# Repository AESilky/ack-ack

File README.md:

# ack-ack
Ack-Ack Robot material. This is a combination of data sheets, schematics, drawings, and code.

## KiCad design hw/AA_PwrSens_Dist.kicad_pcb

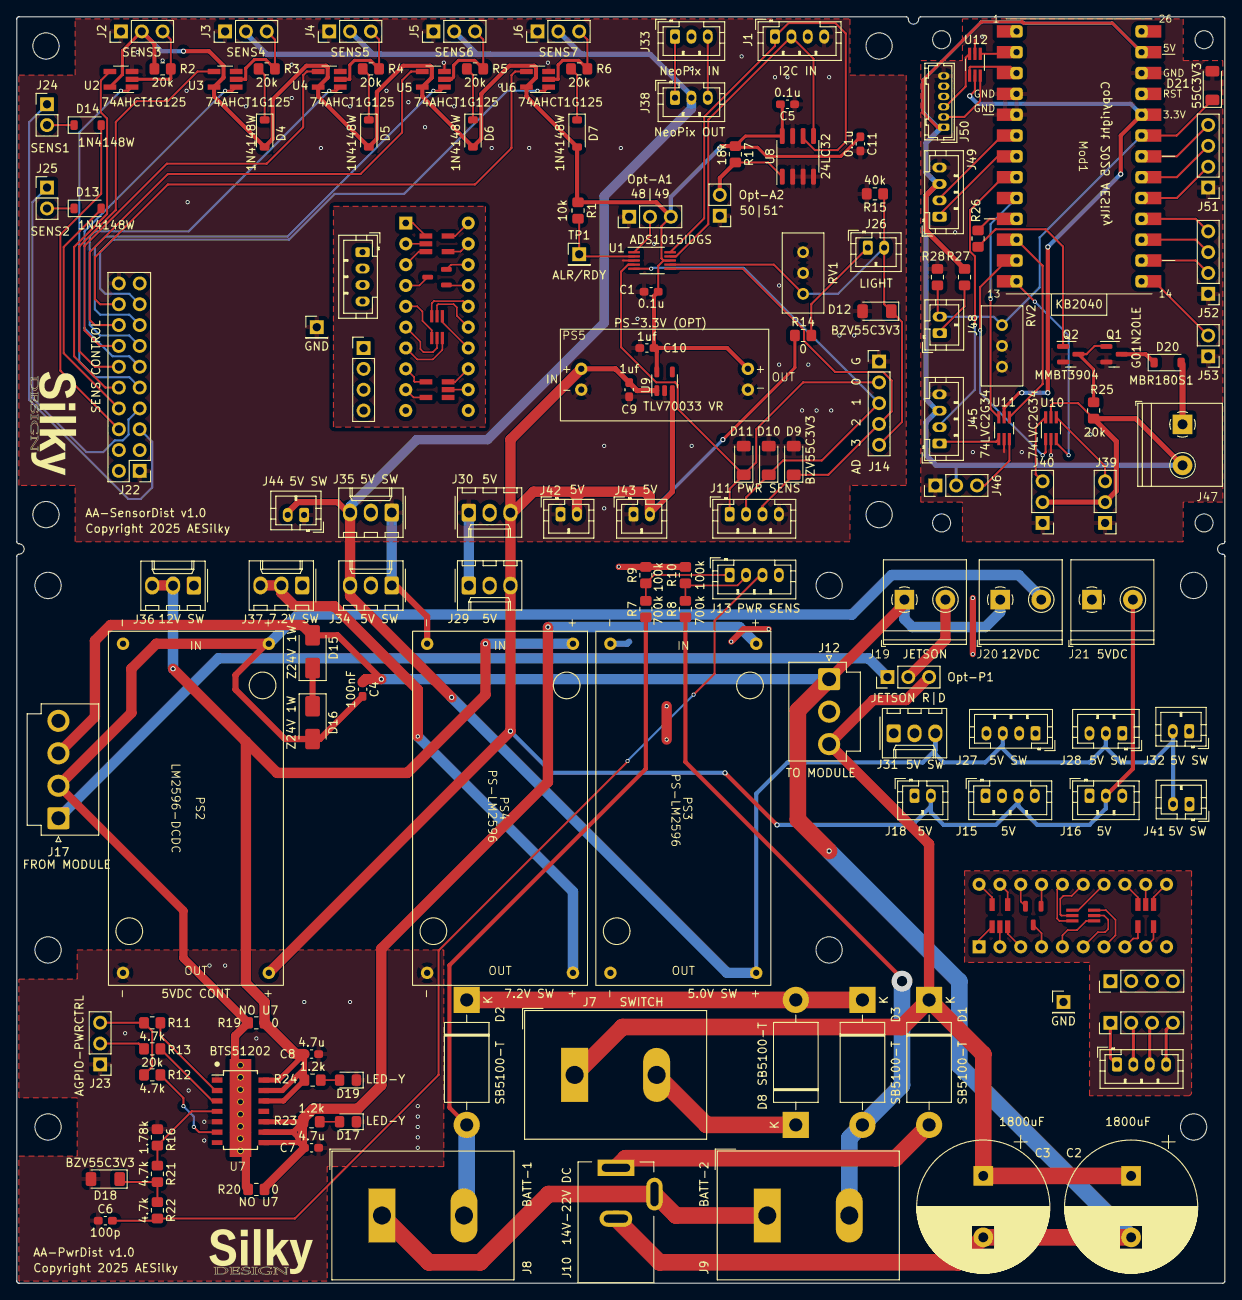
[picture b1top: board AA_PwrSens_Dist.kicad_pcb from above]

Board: 2 copper layers, 147.3 x 154.4 mm, 154 parts (0 on the bottom side), 100 nets.

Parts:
C1, C5, C11: 0.1u; C_0603_1608Metric_Pad1.08x0.95mm_HandSolder
C2, C3: 1800uF; CP_Radial_D16.0mm_P7.50mm
C4: 100nF; C_0603_1608Metric_Pad1.08x0.95mm_HandSolder
C6: 100p; C_0603_1608Metric_Pad1.08x0.95mm_HandSolder
C7, C8: 4.7u; C_0603_1608Metric_Pad1.08x0.95mm_HandSolder
C9, C10: 1uf; C_0603_1608Metric_Pad1.08x0.95mm_HandSolder
D1, D2, D3, D8: SB5100-T; D_DO-201AD_P15.24mm_Horizontal
D4, D5, D6, D7, D13, D14: 1N4148W; D_SOD-123
D9, D10, D11, D12, D18, D21: BZV55C3V3; D_MiniMELF
D15, D16: Z24V 1W; D_SMA
D17, D19: LED-Y; LED_0805_2012Metric_Pad1.15x1.40mm_HandSolder
D20: MBR180S1; D_SOD-123
H1, H2, H3, H4, H5, H6, H7, H8, H9, H10, H11: MountingHole; MountingHole_3.2mm_M3
H13, H14, H15, H16: MH-2mm; MountingHole_2.2mm_M2
J1, J11, J13, J15, J27, J45, J49: JST-PH-B4B; JST_PH_B4B-PH-K_1x04_P2.00mm_Vertical
J2, J3, J4, J5, J6: Conn_01x03; PinHeader_1x03_P2.54mm_Vertical
J7, J8, J9: ScrewLug-2; TerminalBlock_Dinkle_DT-55-B01X-02_P10.00mm
J10: Barrel_Jack_Switch; BarrelJack_Kycon_KLDX-0202-xC_Horizontal
J12: JST-VH-B3P; JST_VH_B3P-VH-B_1x03_P3.96mm_Vertical
J14: Conn_01x05; PinHeader_1x05_P2.54mm_Vertical
J16, J28, J33, J38: JST-PH-B3B; JST_PH_B3B-PH-K_1x03_P2.00mm_Vertical
J17: JST-VH-455-B4P; JST_VH_B4P-VH_1x04_P3.96mm_Vertical
J18, J32, J41: JST-PH-B2B; JST_PH_B2B-PH-K_1x02_P2.00mm_Vertical
J19, J20, J21: SCRW-TERM-2; AES-TermBlock-2POS-5mm-Horz
J22: 20-RBN; PinHeader_2x10_P2.54mm_Vertical
J23: AGPIO-PWRCTRL; PinHeader_1x03_P2.54mm_Vertical
J24, J25: Conn_01x02; PinHeader_1x02_P2.54mm_Vertical
J26, J42, J43, J44, J48: Conn_01x02; JST_PH_B2B-PH-K_1x02_P2.00mm_Vertical
J29, J30, J31, J34, J35, J36, J37: Molex KK-254 AE-6410_1x03; Molex_KK-254_AE-6410-03A_1x03_P2.54mm_Vertical
J39, J40, J46: HDR 1x3 Pin; PinHeader_1x03_P2.54mm_Vertical
J47: ScrewTerm-2; AES-TermBlock-2POS-5mm-Horz
J50: HR-DF13-6P; Hirose_DF13-06P-1.25DSA_1x06_P1.25mm_Vertical
J51, J52: HDR-4; PinHeader_1x04_P2.54mm_Vertical
J53: HDR-2; PinHeader_1x02_P2.54mm_Vertical
Mod1: Adafruit-KB2040-AES
Opt-A1: 3 Pin Hdr; PinHeader_1x03_P2.54mm_Vertical
Opt-A2: Conn_01x02; PinHeader_1x02_P2.54mm_Vertical
Opt-P1: 3 Pin Hdr; PinHeader_1x03_P2.54mm_Vertical
PS2: LM2596-DCDC; DC-DC_Module-AES
PS3, PS4: PS-LM2596; DC-DC_Module-AES
PS5: DC-DC-Mod-1117; DC-DC_Module-SM-44_100-AES
Q1: G01N20LE; SOT-23
Q2: MMBT3904; SOT-23
R1: 10k; R_0805_2012Metric_Pad1.20x1.40mm_HandSolder
R2, R3, R4, R5, R6, R13, R25: 20k; R_0805_2012Metric_Pad1.20x1.40mm_HandSolder
R7, R8: 700.0k; R_0805_2012Metric_Pad1.20x1.40mm_HandSolder
R9, R10: 100.0k; R_0805_2012Metric_Pad1.20x1.40mm_HandSolder
R11, R12, R21, R22: 4.7k; R_0805_2012Metric_Pad1.20x1.40mm_HandSolder
R14, R19, R20, R27: 0; R_0805_2012Metric_Pad1.20x1.40mm_HandSolder
R15, R28: 40k; R_0805_2012Metric_Pad1.20x1.40mm_HandSolder
R16: 1.78k; R_0805_2012Metric_Pad1.20x1.40mm_HandSolder
R17: 18k; R_0805_2012Metric_Pad1.20x1.40mm_HandSolder
R23, R24: 1.2k; R_0805_2012Metric_Pad1.20x1.40mm_HandSolder
R26: 1k; R_0805_2012Metric_Pad1.20x1.40mm_HandSolder
RV1, RV2: 200k; Potentiometer_Bourns_3296W_Vertical
SPR1, SPR1#2: DIP-20_W7.62mm
TP1: 1-Pin; PinHeader_1x01_P2.54mm_Vertical
U1: ADS1015IDGS; VSSOP-10_3x3mm_P0.5mm
U2, U3, U4, U5, U6: 74AHCT1G125; SOT-23-5_HandSoldering
U7: BTS51202; AES-Inf-BTS5120-DSOP14-BP
U8: 24LC32; SOIC-8_3.9x4.9mm_P1.27mm
U9: TLV70033_SOT23-5; SOT-23-5
U10, U11, U12: 74LVC2G34; SOT-363_SC-70-6_Handsoldering

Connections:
+3.3V: C1.2, C5.2, C10.2, C11.1, D4.2 (A), D5.2 (A), D6.2 (A), D7.2 (A), J2.2, Opt-A1.3 (Pin_B), PS5.3 (OUT+), R1.1, R2.1, R17.1, U1.8 (VDD), U2.5 (VCC), U3.5 (VCC), U4.5 (VCC), U5.5 (VCC), U6.5 (VCC), U8.8 (VCC), U9.5 (OUT)
+3.3VP: Mod1.22 (3.3V), U11.5 (VCC), U12.5 (VCC)
+5V: C9.2, J15.3, J16.2, J18.2, J21.2, J29.3, J30.3, J42.2, J43.2, PS2.3 (OUT+), PS5.1 (IN+), R14.1, U9.1 (IN), U9.3 (EN)
+5VD: J3.2, J4.2, J5.2, J6.2, J27.3, J28.2, J31.3, J32.2, J34.3, J35.3, J38.2, J41.2, J44.2, PS3.3 (OUT+)
+5VP: J39.2, J40.2, J45.3, J46.2, J47.2, J49.3, J50.1, Mod1.25 (5V_RAW), R25.2, R27.1, U10.5 (VCC)
+12V: C4.2, D16.2 (A), J17.2, J20.2, PS2.1 (IN+), R19.1, R20.1, U7.CT (VS)
/AA-HeadCtrl/Servo1: J40.3, U10.6
/AA-HeadCtrl/Servo2: J39.3, U10.4
/AIN0: D11.1 (K), J11.1, J14.2, U1.4 (AIN0)
/AIN1: D10.1 (K), J11.2, J14.3, U1.5 (AIN1)
/AIN2: D9.1 (K), J11.3, J14.4, U1.6 (AIN2)
/AIN3: D12.1 (K), J14.5, J26.2, R15.1, RV1.1, U1.7 (AIN3)
/BGND: J8.1, J9.1, J10.3
/BV1: D2.2 (A), J8.2, R7.1
/BV2: D3.2 (A), J9.2, R8.1
/BVC: D2.1 (K), D3.1 (K), D8.2 (A)
/BVC_SW: D8.1 (K), J7.2
/PGND: C2.2, C3.2, C4.1, D15.2 (A), J10.2, J12.1, J17.3, J19.1, J20.1
/PVI: D1.2 (A), J10.1
/PVI_12: J17.1, Opt-P1.1 (Pin_A)
/PVI_SW: C2.1, C3.1, D1.1 (K), J7.1, J12.3, Opt-P1.3 (Pin_B)
/S1-: J22.5, J24.1
/S2-: J22.7, J25.1
/S3-: J22.9, U2.1
/S4-: J22.11, U3.1
/S5-: J22.13, U4.1
/S6-: J22.15, U5.1
/S7-: J22.17, U6.1
/V7_C: J37.2, J37.3, PS4.3 (OUT+)
/V12_C1: C8.2, J36.2, J36.3, PS4.1 (IN+), R19.2, R24.2, U7.12 (OUT0a), U7.13 (OUT0b), U7.14 (OUT0c)
/V12_C2: C7.2, PS3.1 (IN+), R20.2, R23.2, U7.8 (OUT1a), U7.9 (OUT1b), U7.10 (OUT1c)
GND: C1.1, C5.1, C6.1, C7.1, C8.1, C9.1, C10.1, C11.2, D9.2 (A), D10.2 (A), D11.2 (A), D12.2 (A), D17.1 (K), D18.2 (A), D19.1 (K), J1.4, J2.1, J3.1, J4.1, J5.1, J6.1, J11.4, J13.4, J14.1, J15.4, J16.1, J17.4, J18.1, J21.1, J22.1, J22.20, J23.1, J27.4, J28.1, J29.1, J30.1, J31.1, J32.1, J34.1, J35.1, J36.1, J37.1, J41.1, J42.1, J43.1, J44.1, Opt-A1.1 (Pin_A), Opt-A2.1, PS2.2 (IN-), PS2.4 (OUT-), PS3.2 (IN-), PS3.4 (OUT-), PS4.2 (IN-), PS4.4 (OUT-), PS5.2 (IN-), PS5.4 (OUT-), R9.2, R10.2, R15.2, R16.2, RV1.2, RV1.3, U1.3 (GND), U2.3 (GND), U3.3 (GND), U4.3 (GND), U5.3 (GND), U6.3 (GND), U7.1 (GND), U7.5 (DS1), U8.2 (A1), U8.3 (A2), U8.4 (GND), U8.7 (WP), U9.2 (GND)
GND1: D21.2 (A), J39.1, J40.1, J45.4, J46.1, J49.4, J50.6, J51.1, J52.1, J53.1, Mod1.4 (GND), Mod1.5 (GND), Mod1.24 (GND), Q1.2 (S), Q2.2 (E), R28.2, RV2.2, RV2.3, U10.2 (GND), U11.2 (GND), U12.2 (GND)
I2C0_SCL: J1.1, U1.10 (SCL), U8.6 (SCL)
I2C0_SDA: J1.2, U1.9 (SDA), U8.5 (SDA)
unnamed: D4.1 (K), R3.1
unnamed: D5.1 (K), R4.1
unnamed: D6.1 (K), R5.1
unnamed: D7.1 (K), R6.1
unnamed: D13.2 (A), J22.8
unnamed: D13.1 (K), J25.2
unnamed: D14.2 (A), J22.6
unnamed: D14.1 (K), J24.2
unnamed: D15.1 (K), D16.1 (K)
unnamed: D17.2 (A), R23.1
unnamed: D18.1 (K), R21.2, R22.1
unnamed: D19.2 (A), R24.1
unnamed: D20.2 (A), J47.1
unnamed: D20.1 (K), Q1.3 (D)
unnamed: D21.1 (K), J48.2, Mod1.21 (GPIO29_A3), R28.1, RV2.1
unnamed: J2.3, R2.2, U2.2
unnamed: J3.3, R3.2, U3.2
unnamed: J4.3, R4.2, U4.2
unnamed: J5.3, R5.2, U5.2
unnamed: J6.3, R6.2, U6.2
unnamed: J13.1, R7.2, R9.1
unnamed: J13.2, R8.2, R10.1
unnamed: C6.2, J13.3, R22.2
unnamed: J19.2, Opt-P1.2 (Pin_Common)
unnamed: J22.10, U2.4
unnamed: J22.12, U3.4
unnamed: J22.14, U4.4
unnamed: J22.16, U5.4
unnamed: J22.18, U6.4
unnamed: J23.2, R13.1
unnamed: J23.3, R11.1, R12.1
unnamed: J26.1, R14.2
unnamed: J33.1, J38.1
unnamed: J33.3, J38.3
unnamed: J45.1, U11.1
unnamed: J45.2, Mod1.8 (GPIO4_UTX1)
unnamed: J46.3, U11.3
unnamed: J48.1, R27.2
unnamed: J49.1, Mod1.7 (GPIO3_SCL1)
unnamed: J49.2, Mod1.6 (GPIO2_SDA1)
unnamed: J50.2, U12.6
unnamed: J50.3, U12.3
unnamed: J51.2, Mod1.18 (GPIO26_A0)
unnamed: J51.3, Mod1.19 (GPIO27_A1)
unnamed: J51.4, Mod1.20 (GPIO28_A2)
unnamed: J52.2, Mod1.15 (GPIO19_MOSI0)
unnamed: J52.3, Mod1.16 (GPIO20_MISO0)
unnamed: J52.4, Mod1.17 (GPIO18_SCK0)
unnamed: J53.2, Mod1.14 (GPIO10_PWM5A)
unnamed: Mod1.2 (GPIO0_UTX0), U12.1
unnamed: Mod1.3 (GPIO1_URX0), U12.4
unnamed: Mod1.9 (GPIO5_URX1), U11.6
unnamed: Mod1.10 (GPIO6_PWM3A), R26.1
unnamed: Mod1.11 (GPIO7_PWM3B), U11.4
unnamed: Mod1.12 (GPIO8_PWM4A), U10.1
unnamed: Mod1.13 (GPIO9_PWM4B), U10.3
unnamed: Opt-A1.2 (Pin_Common), U1.1 (ADDR)
unnamed: Opt-A2.2, R17.2, U8.1 (A0)
unnamed: Q1.1 (G), Q2.3 (C), R25.1
unnamed: Q2.1 (B), R26.2
unnamed: R1.2, TP1.1, U1.2 (ALERT/RDY)
unnamed: R13.2, U7.3 (DEN)
unnamed: R11.2, U7.2 (IN0)
unnamed: R12.2, U7.6 (IN1)
unnamed: R16.1, R21.1, U7.4 (IS)

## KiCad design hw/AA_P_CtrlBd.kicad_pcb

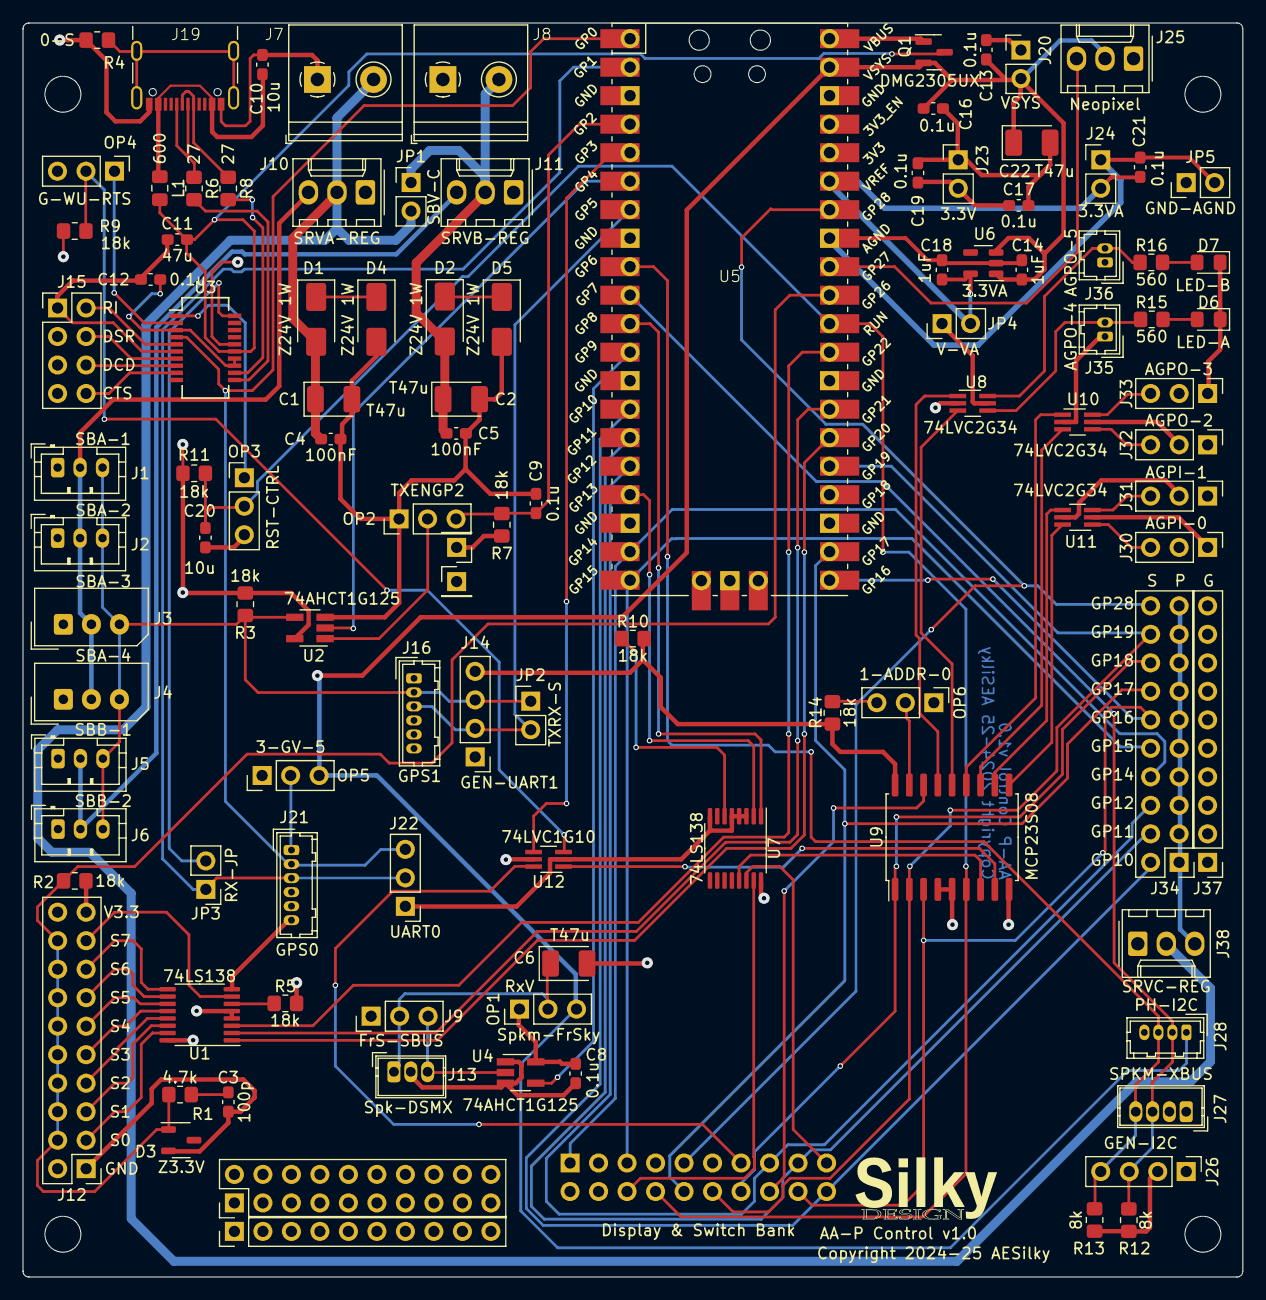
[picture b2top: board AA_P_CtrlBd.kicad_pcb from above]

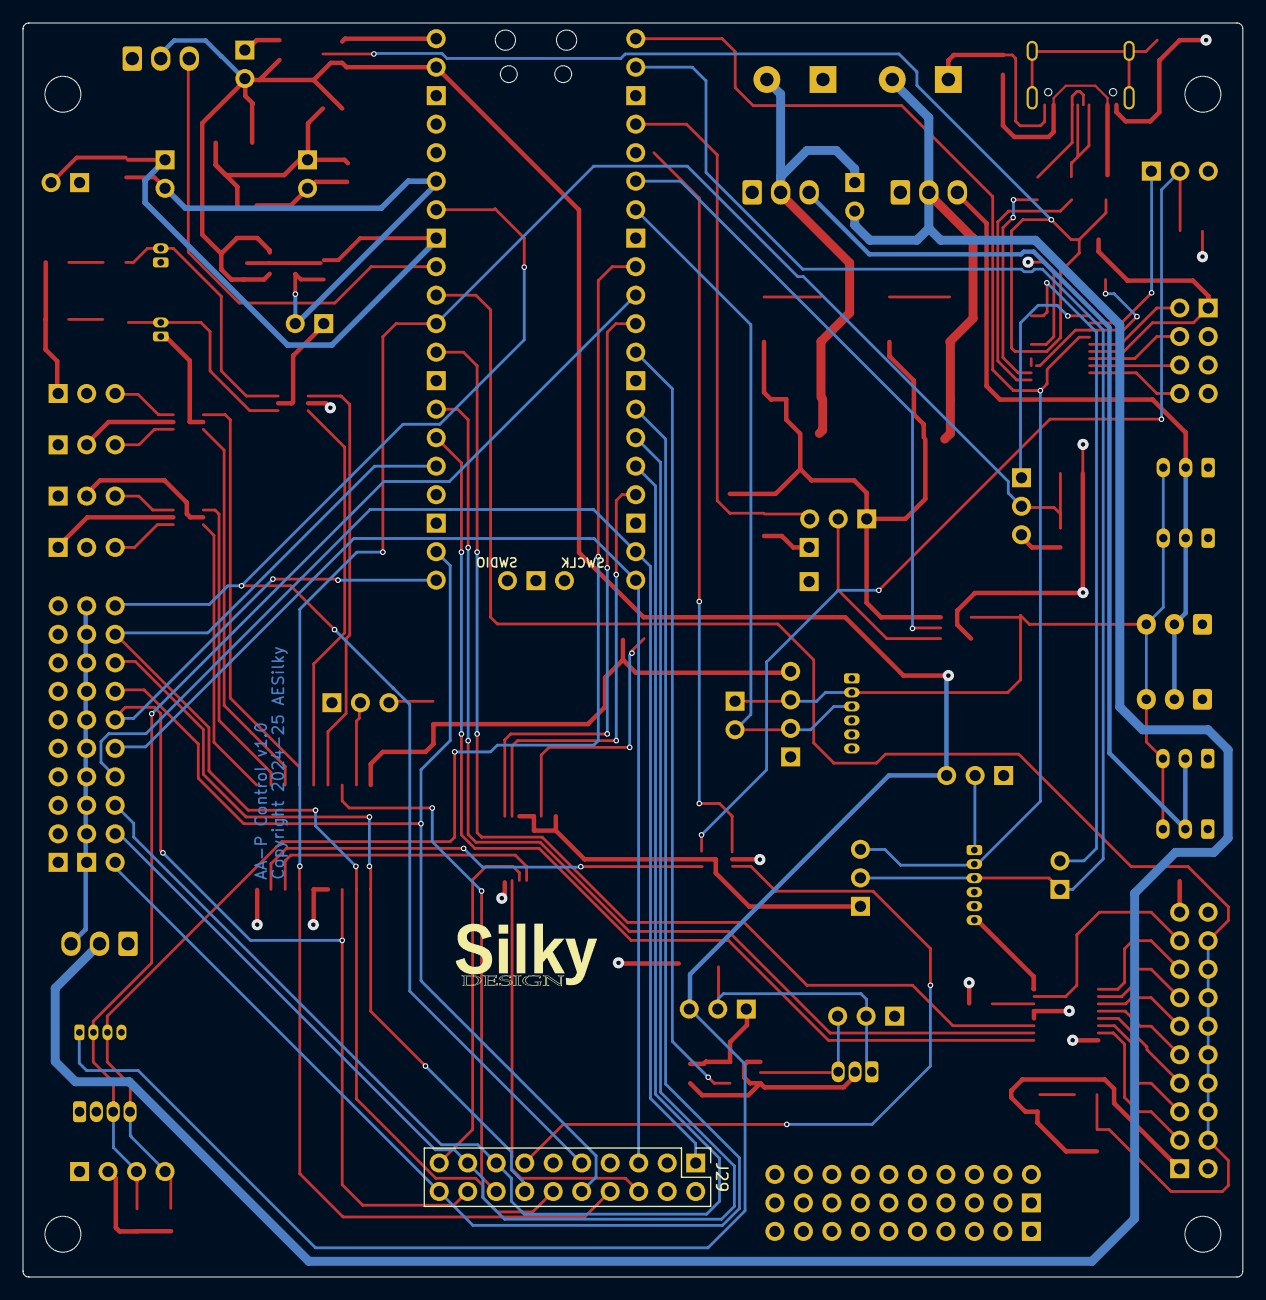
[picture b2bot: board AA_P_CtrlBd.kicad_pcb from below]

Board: 4 copper layers, 108.7 x 111.8 mm, 114 parts (2 on the bottom side), 94 nets.

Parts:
C1, C2, C6, C22: T47u; CP_EIA-3528-21_Kemet-B_Pad1.50x2.35mm_HandSolder
C3: 100p; C_0603_1608Metric_Pad1.08x0.95mm_HandSolder
C4, C5: 100nF; C_0603_1608Metric_Pad1.08x0.95mm_HandSolder
C8, C9, C12, C13, C16, C17, C19, C21: 0.1u; C_0603_1608Metric_Pad1.08x0.95mm_HandSolder
C10, C20: 10u; C_0603_1608Metric_Pad1.08x0.95mm_HandSolder
C11: 47u; C_0603_1608Metric_Pad1.08x0.95mm_HandSolder
C14, C18: 1uF; C_0603_1608Metric_Pad1.08x0.95mm_HandSolder
D1, D2, D4, D5: Z24V 1W; D_SMA
D3: Z3.3V; SOT-23-3
D6: LED-A; LED_0805_2012Metric_Pad1.15x1.40mm_HandSolder
D7: LED-B; LED_0805_2012Metric_Pad1.15x1.40mm_HandSolder
G1, G1#2: LOGO; SILKY-DESIGN-logo-0_50-AES
H1, H2, H3, H4: M3; MountingHole_3.2mm_M3_ISO7380
J1, J2, J5, J6: JST PH-3 2.0; JST_PH_B3B-PH-K_1x03_P2.00mm_Vertical
J3, J4: Molex SP-3 2.5; Molex_SPOX_5267-03A_1x03_P2.50mm_Vertical
J7, J8: SCRW-TERM 2; AES-TermBlock-2POS-5mm-Horz
J9, J22, J30, J31, J32, J33: HDR 1x3 Pin; PinHeader_1x03_P2.54mm_Vertical
J10, J11, J38: Molex KK-254 AE-6410_1x03; Molex_KK-254_AE-6410-03A_1x03_P2.54mm_Vertical
J12: 20-RBN; PinHeader_2x10_P2.54mm_Vertical
J13: JST-B3B-ZR 3 Pin 1.5; Wuerth_WR-WTB_64800311622_1x03_P1.50mm_Vertical
J14: Conn_01x04; PinHeader_1x04_P2.54mm_Vertical
J15: HDR 2x4 Pin Odd/Even; PinHeader_2x04_P2.54mm_Vertical
J16: HR-DF13_6P; Hirose_DF13-06P-1.25DSA_1x06_P1.25mm_Vertical
J17, J18: HDR 1 Pin; PinHeader_1x01_P2.54mm_Vertical
J19: USB-C-Conn; AES-USB_C-Molex-BdTopMnt-2171790001
J20, J23, J24: HDR 1x2 Pin; PinHeader_1x02_P2.54mm_Vertical
J21: HR-DF13-6P; Hirose_DF13-06P-1.25DSA_1x06_P1.25mm_Vertical
J25: HR DF13-3P; Molex_KK-254_AE-6410-03A_1x03_P2.54mm_Vertical
J26: HDR 1x4 Pin; PinHeader_1x04_P2.54mm_Vertical
J27: JST-B4B-ZR 4P 1.5; Wuerth_WR-WTB_64800411622_1x04_P1.50mm_Vertical
J28: HR-DF13-4P 1.25; Hirose_DF13-04P-1.25DSA_1x04_P1.25mm_Vertical
J29, J34: HDR 2x10 Odd/Even; PinHeader_2x10_P2.54mm_Vertical
J35, J36: HR DF13-2P; Hirose_DF13-02P-1.25DSA_1x02_P1.25mm_Vertical
J37: HDR 1x10; PinHeader_1x10_P2.54mm_Vertical
JP1, JP2, JP3, JP4, JP5: HDR 1x2 Pin; PinHeader_1x02_P2.54mm_Vertical
L1: 600RJ0.5A; L_0805_2012Metric_Pad1.15x1.40mm_HandSolder
OP1, OP2, OP3, OP4, OP5, OP6: HDR 1x3 Pin; PinHeader_1x03_P2.54mm_Vertical
Q1: DMG2305UX; SOT-23
R1: 4.7k; R_0805_2012Metric_Pad1.20x1.40mm_HandSolder
R2, R3, R5, R7, R9, R10, R11, R14: 18k; R_0805_2012Metric_Pad1.20x1.40mm_HandSolder
R4: 0-S; R_0805_2012Metric_Pad1.20x1.40mm_HandSolder
R6, R8: 27; R_0805_2012Metric_Pad1.20x1.40mm_HandSolder
R12, R13: 8k; R_0805_2012Metric_Pad1.20x1.40mm_HandSolder
R15, R16: 560; R_0805_2012Metric_Pad1.20x1.40mm_HandSolder
SPARE1: PinHeader_1x10_P2.54mm_Vertical
SPARE2: PinHeader_2x10_P2.54mm_Vertical
U1, U7: 74LS138; TSSOP-16_4.4x5mm_P0.65mm
U2, U4: 74AHCT1G125; SOT-23-5_HandSoldering
U3: FT231XS; SSOP-20_3.9x8.7mm_P0.635mm
U5: AES-Pico; AES-RPi_Pico_SMD_TH
U6: TLV70033_SOT23-5; SOT-23-5
U8, U10, U11: 74LVC2G34; SOT-363_SC-70-6_Handsoldering
U9: AES-MCP23S08-E/SO; SOIC-18W_7.5x11.6mm_P1.27mm
U12: 74LVC1G10; SOT-363_SC-70-6_Handsoldering

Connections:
+3.3V: C8.1, C17.1, C19.2, J12.2, J12.19, J14.4, J16.1, J17.1, J23.2, J26.2, J27.2, J29.2, J30.2, J31.2, J32.2, J33.2, JP4.1 (A), OP1.1 (A), OP5.1 (A), R2.1, R3.2, R5.1, R7.1, R9.1, R10.1, R11.1, R12.2, R13.2, R14.1, U1.16 (VCC), U2.5 (VCC), U4.5 (VCC), U5.36 (3V3), U7.16 (VCC), U8.5 (VCC), U9.18 (VDD), U10.5 (VCC), U11.5 (VCC), U12.5 (VCC)
+3.3VA: C18.1, C21.1, J24.2, J29.11, JP4.2 (B), U5.35 (ADC_VREF), U6.5 (OUT)
/AGP6_DISPBL: J29.16, U9.16 (GP6)
/AUX_GPI0: U9.10 (GP0), U11.6
/AUX_GPI1: U9.11 (GP1), U11.4
/AUX_GPO2: U9.12 (GP2), U10.3
/AUX_GPO3: U9.13 (GP3), U10.1
/AUX_GPO4: U8.3, U9.14 (GP4)
/AUX_GPO5: U8.1, U9.15 (GP5)
/BD_ADDR: OP6.2 (C), U9.17 (GP7)
/CS_A0: U5.11 (GPIO8), U7.1 (A0)
/CS_A1: U5.17 (GPIO13), U7.2 (A1)
/CTS-: J15.8, U3.9 (~CTS)
/DCD-: J15.6, U3.8 (~DCD)
/DISP_CS-: J29.6, U7.15 (O0)
/DSR-: J15.4, U3.7 (~DSR)
/DTR-: OP3.1 (A), U3.1 (~DTR)
/EXIO_CS-: U7.13 (O2), U9.7 (~CS)
/EX_IRQ-: U9.8 (INT), U12.1
/GP10_SPI1_CK: J29.20, J34.2, U5.14 (GPIO10)
/GP11_SPI1_MO: J29.17, J34.4, U5.15 (GPIO11)
/GP12_SPI1_MI: J29.15, J34.6, U5.16 (GPIO12)
/GP14_RE_A: J29.1, J34.8, U5.19 (GPIO14)
/GP15_RE_B: J29.5, J34.10, U5.20 (GPIO15)
/GP16_DE_MISO: J29.18, J34.12, U5.21 (GPIO16), U9.3 (SO)
/GP17_D_D/C-: J29.10, J34.14, U5.22 (GPIO17)
/GP18_DE_SCK: J29.14, J34.16, U5.24 (GPIO18), U9.1 (SCK)
/GP19_DE_MOSI: J29.12, J34.18, U5.25 (GPIO19), U9.2 (SI)
/GP27A1_NEOPXL: J25.3, U5.32 (GPIO27_ADC1)
/GP28A2_SWMX: J29.9, J34.20, U5.34 (GPIO28_ADC2)
/I2C0_SCL: J26.3, J27.3, J28.2, R12.1, U5.10 (GPIO7)
/I2C0_SDA: J26.4, J27.4, J28.3, R13.1, U5.9 (GPIO6)
/RCVR_IN: U4.4, U5.12 (GPIO9)
/RCVR_RX: J9.3, J13.3, U4.2
/RESET-: C20.2, J29.8, OP3.2 (C), R11.2, U5.30 (RUN), U9.6 (~RESET)
/RI-: J15.2, U3.5 (~RI)
/RTS-: OP4.1 (A), U3.2 (~RTS)
/RxPWR: C6.1, J9.2, J13.1, OP1.2 (C)
/S0-: J12.3, U1.15 (O0)
/S1-: J12.5, U1.14 (O1)
/S2-: J12.7, U1.13 (O2)
/S3-: J12.9, U1.12 (O3)
/S4-: J12.11, U1.11 (O4)
/S5-: J12.13, U1.10 (O5)
/S6-: J12.15, U1.9 (O6)
/S7-: J12.17, U1.7 (O7)
/SBA_RP: J1.2, J2.2, J3.2, J4.2, J10.3 (B)
/SBB_RP: J5.2, J6.2, J11.3 (B)
/SBC_RP: J34.1, J34.3, J34.5, J34.7, J34.9, J34.11, J34.13, J34.15, J34.17, J34.19, J38.3 (B)
/SB_TX_EN-: C9.1, OP2.3 (B), R7.2, U5.4 (GPIO2)
/SENS_A0: U1.1 (A0), U5.26 (GPIO20)
/SENS_A1: U1.2 (A1), U5.27 (GPIO21)
/SENS_A2: U1.3 (A2), U5.29 (GPIO22)
/SENS_RD-: D3.1 (K), J12.4, J12.6, J12.8, J12.10, J12.12, J12.14, J12.16, J12.18, R1.1, R2.2, U5.31 (GPIO26_ADC0)
/TCH_CS-: J29.19, U7.14 (O1)
/TCH_IRQ-: J29.13, U12.6
/UART0_RX: J21.3, J22.2, JP3.1 (A), U5.2 (GPIO1)
/UART0_TX: J21.2, J22.3, U3.4 (RXD), U5.1 (GPIO0)
/UART1_RX: J14.2, J16.3, JP2.2 (B), U5.7 (GPIO5)
/UART1_TX: U2.2, U5.6 (GPIO4)
/VBUS: Q1.1 (G), U5.40 (VBUS)
/VBUS_IF: C11.2, L1.2, Q1.3 (D), U3.15 (VCC)
/VBUS_IN: C10.2, J19.A4_B9 (VBUS), J19.B4_A9 (VBUS), L1.1
/WAKEUP-: OP4.2 (C), R9.2, U12.3
/WU_IRQ: U5.5 (GPIO3), U12.4
GND: C1.2, C2.2, C3.1, C4.2, C5.2, C6.2, C8.2, C9.2, C10.1, C11.1, C12.2, C13.1, C16.2, C17.2, C19.1, C20.1, C22.2, D3.2 (A), D4.2 (A), D5.2 (A), D6.1 (K), D7.1 (K), J1.1, J2.1, J3.1, J4.1, J5.1, J6.1, J7.1, J8.1, J9.1, J10.1 (A), J11.1 (A), J12.1, J12.20, J13.2, J14.1, J15.1, J15.3, J15.5, J15.7, J16.6, J18.1, J19.A1_B12 (GND), J19.B1_A12 (GND), J20.1, J21.6, J22.1, J23.1, J25.1, J26.1, J27.1, J28.4, J29.3, J29.7, J30.1, J31.1, J32.1, J33.1, J35.1, J36.1, J37.1, J37.2, J37.3, J37.4, J37.5, J37.6, J37.7, J37.8, J37.9, J37.10, J38.1 (A), JP5.1 (A), OP2.1 (A), OP3.3 (B), OP4.3 (B), OP6.1 (A), R4.1, U1.4 (E1), U1.5 (E2), U1.8 (GND), U2.3 (GND), U3.6 (GND), U3.16 (GND), U4.1, U4.3 (GND), U5.3 (GND), U5.8 (GND), U5.13 (GND), U5.18 (GND), U5.23 (GND), U5.28 (GND), U5.38 (GND), U7.3 (A2), U7.4 (E1), U7.5 (E2), U7.8 (GND), U8.2 (GND), U9.4 (A1), U9.5 (A0), U9.9 (VSS), U10.2 (GND), U11.2 (GND), U12.2 (GND)
GNDA: C14.2, C18.2, C21.2, J24.1, J29.4, JP5.2 (B), U5.33 (AGND), U6.2 (GND)
unnamed: C3.2, R1.2
unnamed: D1.1 (K), D4.1 (K)
unnamed: D2.1 (K), D5.1 (K)
unnamed: D6.2 (A), R15.1
unnamed: D7.2 (A), R16.1
unnamed: J1.3, J2.3, J3.3, J4.3, J5.3, J6.3, J14.3, J16.2, JP2.1 (A), R3.1, U2.4
unnamed: J19.A6 (D+), J19.B6 (D+), R6.1
unnamed: J19.A7 (D-), J19.B7 (D-), R8.1
unnamed: J19.SH1 (SHIELD), J19.SH2 (SHIELD), J19.SH3 (SHIELD), J19.SH4 (SHIELD), R4.2
unnamed: J21.1, OP5.2 (C)
unnamed: J30.3, U11.1
unnamed: J31.3, U11.3
unnamed: J32.3, U10.4
unnamed: J33.3, U10.6
unnamed: J35.2, R15.2, U8.4
unnamed: J36.2, R16.2, U8.6
unnamed: JP3.2 (B), U3.20 (TXD)
unnamed: OP2.2 (C), U2.1
unnamed: OP6.3 (B), R14.2
unnamed: R5.2, U1.6 (E3)
unnamed: C12.1, U3.3 (VCCIO), U3.13 (3V3OUT), U3.14 (~RESET)
unnamed: R8.2, U3.12 (USBDM)
unnamed: R6.2, U3.11 (USBDP)
unnamed: R10.2, U7.6 (E3)
VS-BA: C1.1, C4.1, D1.2 (A), J7.2, J10.2 (C), J38.2 (C), JP1.2 (B)
VS-BB: C2.1, C5.1, D2.2 (A), J8.2, J11.2 (C), JP1.1 (A)
VSYS: C13.2, C14.1, C16.1, C22.1, J20.2, J25.2, J28.1, OP1.3 (B), OP5.3 (B), Q1.2 (S), U5.39 (VSYS), U6.1 (IN), U6.3 (EN)

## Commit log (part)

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2019-10-23 Update README.md
    Initial content.
2019-12-15 Initial Arduino from SS balancing bot (see for added files)
2024-09-06 PICO: Separate Pico/Arduino. Pico Servo & Receiver.
2024-09-06 COMP: INA3221 Datasheet.
2024-09-07 PWRMON: Added module for INA3221 Power Monitor.
2024-09-08 PWRMON: Add WARN&CRIT status.
2024-11-03 HW: Start control board.
2024-11-03 Pico-Control-Board v1
2024-11-14 HW: Ready for layout.
2024-11-22 4" Display, Rotary, Cursor Buttons, Bus-Servo control, High/Normal/Low Priority Q
2024-11-23 Touch returns panel, screen, display position.
2024-11-25 Sch: Remove pwr-ctrl. Add exgpio conns.
2024-11-27 Term and Touch-Keyboard starting to work.
2024-12-03 CTRL-BD-Pico: v1.0 to send for PCB.
2024-12-30 IBOM generated.
2025-01-04 Display, touch, servos, new messaging.
2025-01-10 RP2350 Control Board v1.0 running. Display, curswitch, sensbank, expio, touch.
2025-01-19 Neopixel panel working
2025-01-29 Add NeoPixel. Improve stats.
2025-02-01 HW: Add pdf schematic of the Pico Ctrl board.
2025-02-01 Docs: Add Sojourner info.
2025-02-22 CDoc: Add NVIDIA Jetson design doc
2025-05-17 Significant Pico-CTRL progress
2025-05-20 Ctrl: RX SBUS detected and messages received (not decoding yet)
2025-05-20 CMT: Remove L9 queue (only use NP & LP). HWRT: Change from HWOS.
2025-05-29 RC-RX: SBUS and SRXL2 implemented.
2025-05-29 Reorganize the message loop processing.
2025-05-30 HW: Pwr & Sens board and parts.
2025-05-30 RCRX: Block on PUSH.
2025-06-11 RCRX: SBUS working. SRXL2 working as much as testable.
2025-06-14 Board 0 and 1 project build. MAVLink RC channel values.
2025-06-15 DCS Re-org. Start of DCS RC 'Direct-Control'.
2025-06-16 DCS Handle Fwd-Rot-Rev RC control.
2025-06-19 SM/Sleep reimplemented. HID changed to HID_NAV.
2025-06-21 Scheduled Msg fix alloc/return. DCS process steering and throttle.
2025-06-21 CMT: Remove LOW-PRIORITY messages and dual queues to avoid starving messages.
2025-07-05 DCS RC: Direct control functional.
2025-07-12 ADC: Added module for ADS1015.
2025-07-24 HWRT compile as 0 or 1. ADC and EEPROM added.
2025-07-24 Doc: Add wheels geometry drawing (velocity and yaw calc).
2025-07-26 PCB: Files for PCB rev 1.0
2025-08-08 First Run
2025-08-20 Sensbank: Buttons and sonar/lidar working. CMT: Re-org SM.
2025-08-21 STOP Switch functional.
2025-08-24 Tone and Melodies.

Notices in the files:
hw/AA_P_CtrlBd.kicad_pcb:
Copyright 2024, AES
Copyright 2024-25 AESilky
hw/AA_PwrSens_Dist.kicad_pcb:
Copyright 2025 AESilky
